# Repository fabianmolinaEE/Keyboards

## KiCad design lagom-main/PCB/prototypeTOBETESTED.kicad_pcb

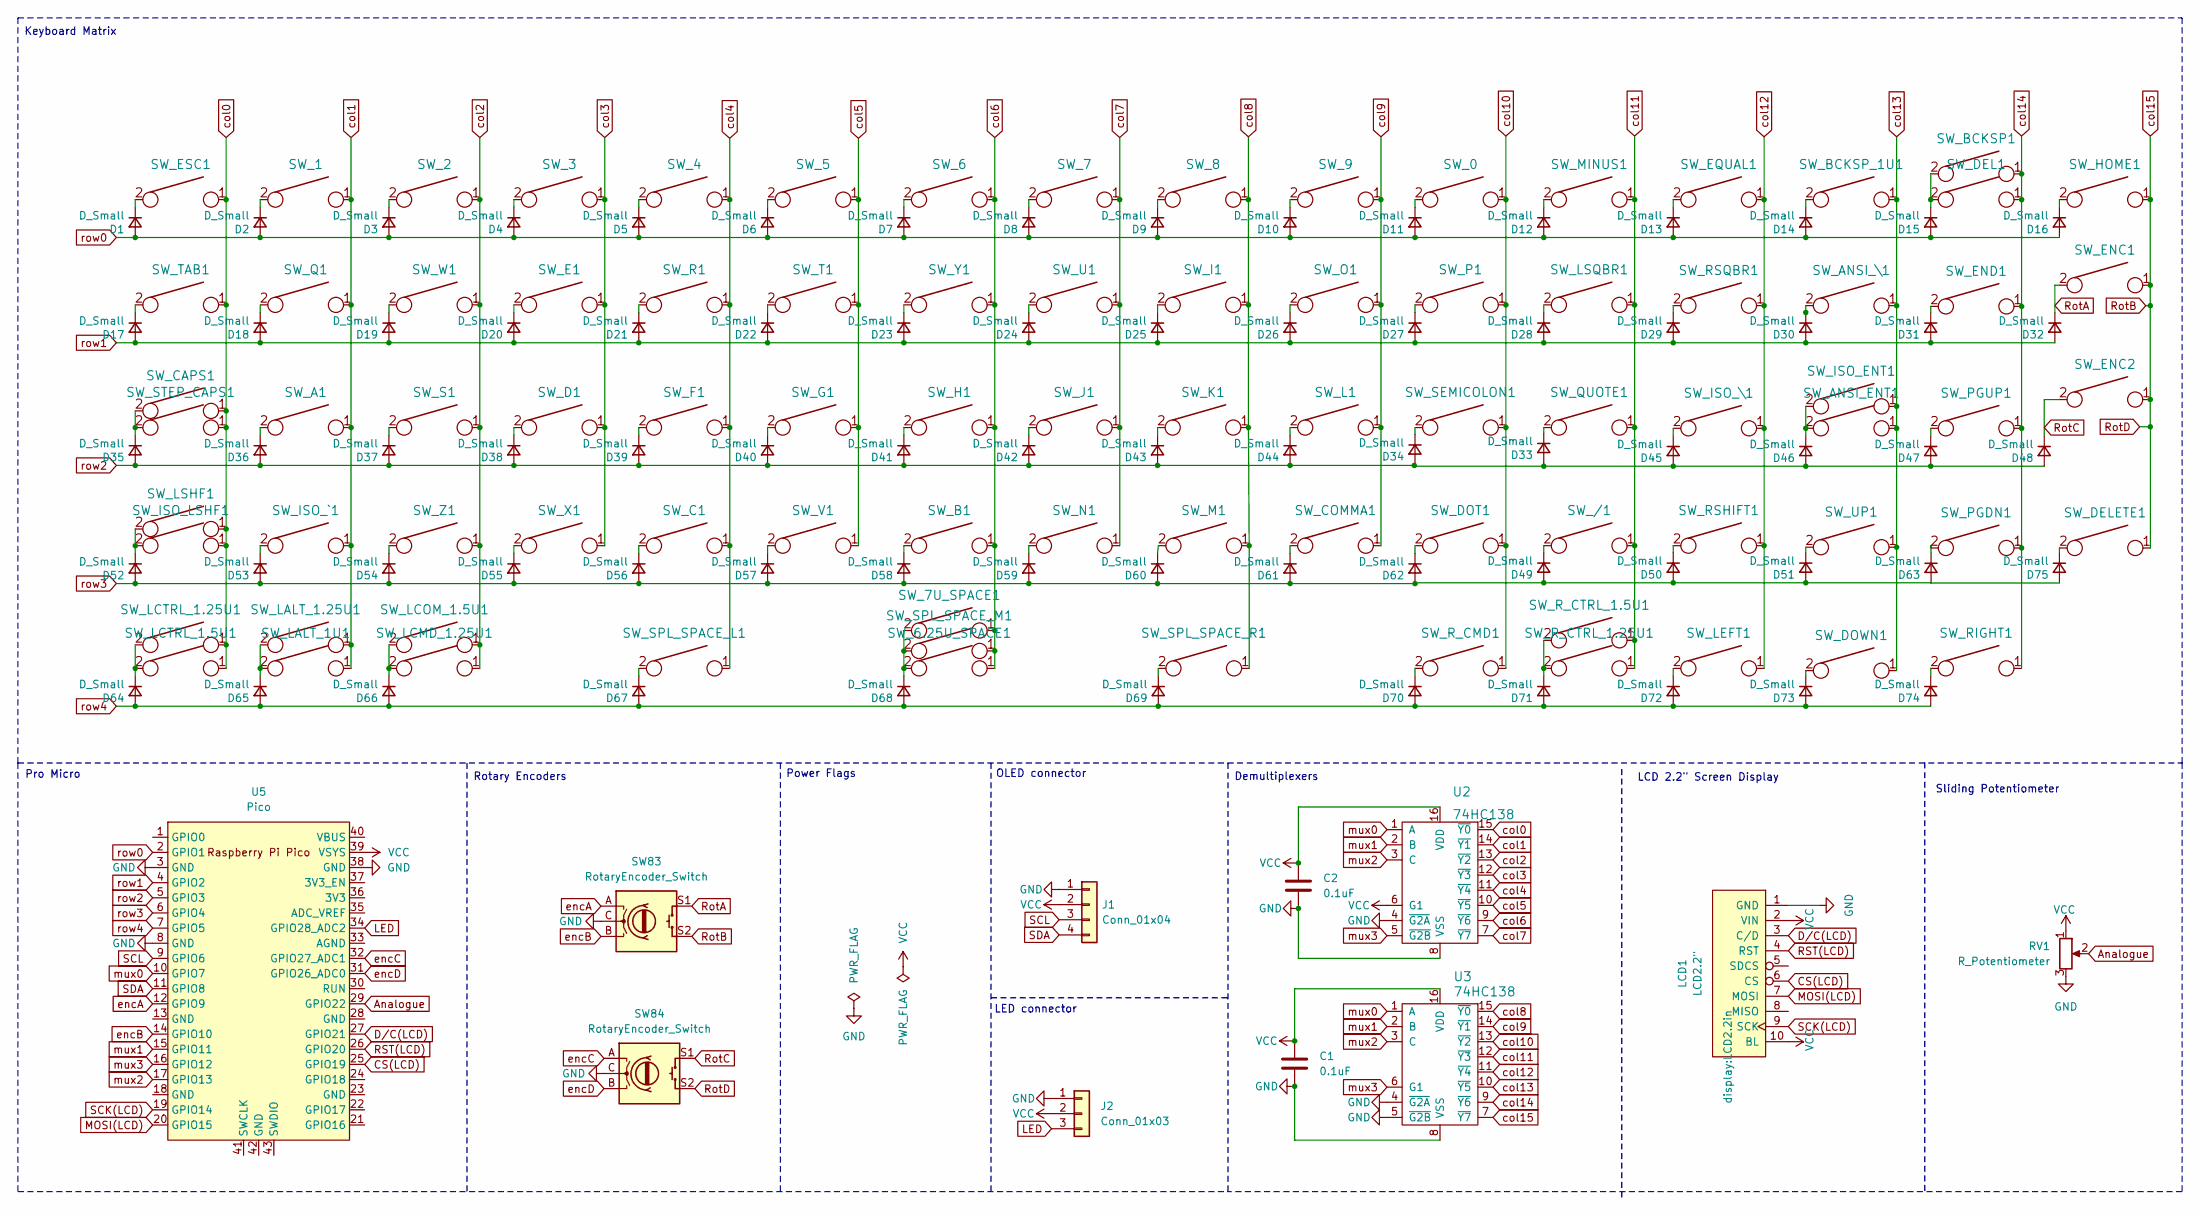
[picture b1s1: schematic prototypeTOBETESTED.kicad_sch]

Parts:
C1, C2: 0.1uF; C_Disc_D4.7mm_W2.5mm_P5.00mm
D1, D2, D3, D4, D5, D6, D7, D8, D9, D10, D11, D12, D13, D14, D15, D16, D17, D18, D19, D20, D21, D22, D23, D24, D25, D26, D27, D28, D29, D30, D31, D32, D33, D34, D35, D36, D37, D38, D39, D40, D41, D42, D43, D44, D45, D46, D47, D48, D49, D50, D51, D52, D53, D54, D55, D56, D57, D58, D59, D60, D61, D62, D63, D64, D65, D66, D67, D68, D69, D70, D71, D72, D73, D74, D75: D_Small; D_DO-34_SOD68_P7.62mm_Horizontal
J1: Conn_01x04; PinSocket_1x04_P2.54mm_Vertical
J2: Conn_01x03; PinSocket_1x03_P2.54mm_Vertical
LCD1: LCD2.2"; LCD2.2in
RV1: R_Potentiometer; Potentiometer_Bourns_PTA6043_Single_Slide
SW83, SW84: RotaryEncoder_Switch; RotaryEncoder_EC11
SW_0, SW_1, SW_2, SW_3, SW_4, SW_5, SW_6, SW_7, SW_8, SW_9: KEYSW; SW_Cherry_MX_1.00u_PCB
SW_6.25U_SPACE1: KEYSW; SW_Cherry_MX_6.25u_PCB
SW_7U_SPACE1: KEYSW; SW_Cherry_MX_7u_PCB
SW_/1: KEYSW; SW_Cherry_MX_1.00u_PCB
SW_A1: KEYSW; SW_Cherry_MX_1.00u_PCB
SW_ANSI_ENT1: KEYSW; SW_Cherry_MX_2.25u_PCB
SW_ANSI_\1: KEYSW; SW_Cherry_MX_1.50u_PCB
SW_B1: KEYSW; SW_Cherry_MX_1.00u_PCB
SW_BCKSP1: KEYSW; SW_Cherry_MX_2.00u_PCB
SW_BCKSP_1U1: KEYSW; SW_Cherry_MX_1.00u_PCB
SW_C1: KEYSW; SW_Cherry_MX_1.00u_PCB
SW_CAPS1: KEYSW; SW_Cherry_MX_1.75u_PCB
SW_COMMA1: KEYSW; SW_Cherry_MX_1.00u_PCB
SW_D1: KEYSW; SW_Cherry_MX_1.00u_PCB
SW_DEL1: KEYSW; SW_Cherry_MX_1.00u_PCB
SW_DELETE1: KEYSW; SW_Cherry_MX_1.00u_PCB
SW_DOT1: KEYSW; SW_Cherry_MX_1.00u_PCB
SW_DOWN1: KEYSW; SW_Cherry_MX_1.00u_PCB
SW_E1: KEYSW; SW_Cherry_MX_1.00u_PCB
SW_ENC1, SW_ENC2: KEYSW; SW_Cherry_MX_1.00u_PCB
SW_END1: KEYSW; SW_Cherry_MX_1.00u_PCB
SW_EQUAL1: KEYSW; SW_Cherry_MX_1.00u_PCB
SW_ESC1: KEYSW; SW_Cherry_MX_1.00u_PCB
SW_F1: KEYSW; SW_Cherry_MX_1.00u_PCB
SW_G1: KEYSW; SW_Cherry_MX_1.00u_PCB
SW_H1: KEYSW; SW_Cherry_MX_1.00u_PCB
SW_HOME1: KEYSW; SW_Cherry_MX_1.00u_PCB
SW_I1: KEYSW; SW_Cherry_MX_1.00u_PCB
SW_ISO_ENT1: KEYSW; SW_Cherry_MX_ISOEnter_PCB_Flipped_Rotated
SW_ISO_LSHF1: KEYSW; SW_Cherry_MX_1.25u_PCB
SW_ISO_\1: KEYSW; SW_Cherry_MX_1.00u_PCB
SW_ISO_`1: KEYSW; SW_Cherry_MX_1.00u_PCB
SW_J1: KEYSW; SW_Cherry_MX_1.00u_PCB
SW_K1: KEYSW; SW_Cherry_MX_1.00u_PCB
SW_L1: KEYSW; SW_Cherry_MX_1.00u_PCB
SW_LALT_1.25U1: KEYSW; SW_Cherry_MX_1.25u_PCB
SW_LALT_1U1: KEYSW; SW_Cherry_MX_1.00u_PCB
SW_LCMD_1.25U1: KEYSW; SW_Cherry_MX_1.25u_PCB
SW_LCOM_1.5U1: KEYSW; SW_Cherry_MX_1.50u_PCB
SW_LCTRL_1.5U1: KEYSW; SW_Cherry_MX_1.50u_PCB
SW_LCTRL_1.25U1: KEYSW; SW_Cherry_MX_1.25u_PCB
SW_LEFT1: KEYSW; SW_Cherry_MX_1.00u_PCB
SW_LSHF1: KEYSW; SW_Cherry_MX_2.25u_PCB
SW_LSQBR1: KEYSW; SW_Cherry_MX_1.00u_PCB
SW_M1: KEYSW; SW_Cherry_MX_1.00u_PCB
SW_MINUS1: KEYSW; SW_Cherry_MX_1.00u_PCB
SW_N1: KEYSW; SW_Cherry_MX_1.00u_PCB
SW_O1: KEYSW; SW_Cherry_MX_1.00u_PCB
SW_P1: KEYSW; SW_Cherry_MX_1.00u_PCB
SW_PGDN1: KEYSW; SW_Cherry_MX_1.00u_PCB
SW_PGUP1: KEYSW; SW_Cherry_MX_1.00u_PCB
SW_Q1: KEYSW; SW_Cherry_MX_1.00u_PCB
SW_QUOTE1: KEYSW; SW_Cherry_MX_1.00u_PCB
SW_R1: KEYSW; SW_Cherry_MX_1.00u_PCB
SW_RIGHT1: KEYSW; SW_Cherry_MX_1.00u_PCB
SW_RSHIFT1: KEYSW; SW_Cherry_MX_1.75u_PCB
SW_RSQBR1: KEYSW; SW_Cherry_MX_1.00u_PCB
SW_R_CMD1: KEYSW; SW_Cherry_MX_1.25u_PCB
SW_R_CTRL_1.5U1: KEYSW; SW_Cherry_MX_1.50u_PCB
SW_R_CTRL_1.25U1: KEYSW; SW_Cherry_MX_1.25u_PCB
SW_S1: KEYSW; SW_Cherry_MX_1.00u_PCB
SW_SEMICOLON1: KEYSW; SW_Cherry_MX_1.00u_PCB
SW_SPL_SPACE_L1: KEYSW; SW_Cherry_MX_2.25u_PCB
SW_SPL_SPACE_M1: KEYSW; SW_Cherry_MX_1.25u_PCB
SW_SPL_SPACE_R1: KEYSW; SW_Cherry_MX_2.75u_PCB
SW_STEP_CAPS1: KEYSW; SW_Cherry_MX_1.25u_PCB
SW_T1: KEYSW; SW_Cherry_MX_1.00u_PCB
SW_TAB1: KEYSW; SW_Cherry_MX_1.50u_Plate
SW_U1: KEYSW; SW_Cherry_MX_1.00u_PCB
SW_UP1: KEYSW; SW_Cherry_MX_1.00u_PCB
SW_V1: KEYSW; SW_Cherry_MX_1.00u_PCB
SW_W1: KEYSW; SW_Cherry_MX_1.00u_PCB
SW_X1: KEYSW; SW_Cherry_MX_1.00u_PCB
SW_Y1: KEYSW; SW_Cherry_MX_1.00u_PCB
SW_Z1: KEYSW; SW_Cherry_MX_1.00u_PCB
U2, U3: 74HC138; DIP-16_W7.62mm_Socket
U5: Pico; RPi_Pico_SMD_TH

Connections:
Analogue: RV1.2, U5.29 (GPIO22)
CS(LCD): LCD1.6 (CS), U5.25 (GPIO19)
D/C(LCD): LCD1.3 (C/D), U5.27 (GPIO21)
GND: C1.2, C2.2, J1.1, J2.1, LCD1.1 (GND), RV1.3, SW83.C, SW84.C, U2.4 (~G2A), U2.8 (VSS), U3.4 (~G2A), U3.5 (~G2B), U3.8 (VSS), U5.3 (GND), U5.8 (GND), U5.38 (GND)
LED: J2.3, U5.34 (GPIO28_ADC2)
MOSI(LCD): LCD1.7 (MOSI), U5.20 (GPIO15)
unnamed: D1.1 (K), SW_ESC1.2
unnamed: D2.1 (K), SW_1.2
unnamed: D3.1 (K), SW_2.2
unnamed: D4.1 (K), SW_3.2
unnamed: D5.1 (K), SW_4.2
unnamed: D6.1 (K), SW_5.2
unnamed: D7.1 (K), SW_6.2
unnamed: D8.1 (K), SW_7.2
unnamed: D9.1 (K), SW_8.2
unnamed: D10.1 (K), SW_9.2
unnamed: D11.1 (K), SW_0.2
unnamed: D12.1 (K), SW_MINUS1.2
unnamed: D13.1 (K), SW_EQUAL1.2
unnamed: D14.1 (K), SW_BCKSP_1U1.2
unnamed: D15.1 (K), SW_BCKSP1.2, SW_DEL1.2
unnamed: D16.1 (K), SW_HOME1.2
unnamed: D17.1 (K), SW_TAB1.2
unnamed: D18.1 (K), SW_Q1.2
unnamed: D19.1 (K), SW_W1.2
unnamed: D20.1 (K), SW_E1.2
unnamed: D21.1 (K), SW_R1.2
unnamed: D22.1 (K), SW_T1.2
unnamed: D23.1 (K), SW_Y1.2
unnamed: D24.1 (K), SW_U1.2
unnamed: D25.1 (K), SW_I1.2
unnamed: D26.1 (K), SW_O1.2
unnamed: D27.1 (K), SW_P1.2
unnamed: D28.1 (K), SW_LSQBR1.2
unnamed: D29.1 (K), SW_RSQBR1.2
unnamed: D30.1 (K), SW_ANSI_\1.2
unnamed: D31.1 (K), SW_END1.2
unnamed: D33.1 (K), SW_QUOTE1.2
unnamed: D34.1 (K), SW_SEMICOLON1.2
unnamed: D35.1 (K), SW_CAPS1.2, SW_STEP_CAPS1.2
unnamed: D36.1 (K), SW_A1.2
unnamed: D37.1 (K), SW_S1.2
unnamed: D38.1 (K), SW_D1.2
unnamed: D39.1 (K), SW_F1.2
unnamed: D40.1 (K), SW_G1.2
unnamed: D41.1 (K), SW_H1.2
unnamed: D42.1 (K), SW_J1.2
unnamed: D43.1 (K), SW_K1.2
unnamed: D44.1 (K), SW_L1.2
unnamed: D45.1 (K), SW_ISO_\1.2
unnamed: D46.1 (K), SW_ANSI_ENT1.2, SW_ISO_ENT1.2
unnamed: D47.1 (K), SW_PGUP1.2
unnamed: D49.1 (K), SW_/1.2
unnamed: D50.1 (K), SW_RSHIFT1.2
unnamed: D51.1 (K), SW_UP1.2
unnamed: D52.1 (K), SW_ISO_LSHF1.2, SW_LSHF1.2
unnamed: D53.1 (K), SW_ISO_`1.2
unnamed: D54.1 (K), SW_Z1.2
unnamed: D55.1 (K), SW_X1.2
unnamed: D56.1 (K), SW_C1.2
unnamed: D57.1 (K), SW_V1.2
unnamed: D58.1 (K), SW_B1.2
unnamed: D59.1 (K), SW_N1.2
unnamed: D60.1 (K), SW_M1.2
unnamed: D61.1 (K), SW_COMMA1.2
unnamed: D62.1 (K), SW_DOT1.2
unnamed: D63.1 (K), SW_PGDN1.2
unnamed: D64.1 (K), SW_LCTRL_1.5U1.2, SW_LCTRL_1.25U1.2
unnamed: D65.1 (K), SW_LALT_1.25U1.2, SW_LALT_1U1.2
unnamed: D66.1 (K), SW_LCMD_1.25U1.2, SW_LCOM_1.5U1.2
unnamed: D67.1 (K), SW_SPL_SPACE_L1.2
unnamed: D68.1 (K), SW_6.25U_SPACE1.2, SW_7U_SPACE1.2, SW_SPL_SPACE_M1.2
unnamed: D69.1 (K), SW_SPL_SPACE_R1.2
unnamed: D70.1 (K), SW_R_CMD1.2
unnamed: D71.1 (K), SW_R_CTRL_1.5U1.2, SW_R_CTRL_1.25U1.2
unnamed: D72.1 (K), SW_LEFT1.2
unnamed: D73.1 (K), SW_DOWN1.2
unnamed: D74.1 (K), SW_RIGHT1.2
unnamed: D75.1 (K), SW_DELETE1.2
RST(LCD): LCD1.4 (RST), U5.26 (GPIO20)
RotA: D32.1 (K), SW83.S1, SW_ENC1.2
RotB: SW83.S2, SW84.S2, SW_DELETE1.1, SW_ENC1.1, SW_ENC2.1, SW_HOME1.1, U3.7 (~Y7)
RotC: D48.1 (K), SW84.S1, SW_ENC2.2
SCK(LCD): LCD1.9 (SCK), U5.19 (GPIO14)
SCL: J1.3, U5.9 (GPIO6)
SDA: J1.4, U5.11 (GPIO8)
VCC: C1.1, C2.1, J1.2, J2.2, LCD1.2 (VIN), LCD1.10 (BL), RV1.1, U2.6 (G1), U2.16 (VDD), U3.16 (VDD), U5.39 (VSYS)
col0: SW_CAPS1.1, SW_ESC1.1, SW_ISO_LSHF1.1, SW_LCTRL_1.5U1.1, SW_LCTRL_1.25U1.1, SW_LSHF1.1, SW_STEP_CAPS1.1, SW_TAB1.1, U2.15 (~Y0)
col1: SW_1.1, SW_A1.1, SW_ISO_`1.1, SW_LALT_1.25U1.1, SW_LALT_1U1.1, SW_Q1.1, U2.14 (~Y1)
col2: SW_2.1, SW_LCMD_1.25U1.1, SW_LCOM_1.5U1.1, SW_S1.1, SW_W1.1, SW_Z1.1, U2.13 (~Y2)
col3: SW_3.1, SW_D1.1, SW_E1.1, SW_X1.1, U2.12 (~Y3)
col4: SW_4.1, SW_C1.1, SW_F1.1, SW_R1.1, SW_SPL_SPACE_L1.1, U2.11 (~Y4)
col5: SW_5.1, SW_G1.1, SW_T1.1, SW_V1.1, U2.10 (~Y5)
col6: SW_6.1, SW_6.25U_SPACE1.1, SW_7U_SPACE1.1, SW_B1.1, SW_H1.1, SW_SPL_SPACE_M1.1, SW_Y1.1, U2.9 (~Y6)
col7: SW_7.1, SW_J1.1, SW_N1.1, SW_U1.1, U2.7 (~Y7)
col8: SW_8.1, SW_I1.1, SW_K1.1, SW_M1.1, SW_SPL_SPACE_R1.1, U3.15 (~Y0)
col9: SW_9.1, SW_COMMA1.1, SW_L1.1, SW_O1.1, U3.14 (~Y1)
col10: SW_0.1, SW_DOT1.1, SW_P1.1, SW_R_CMD1.1, SW_SEMICOLON1.1, U3.13 (~Y2)
col11: SW_/1.1, SW_LSQBR1.1, SW_MINUS1.1, SW_QUOTE1.1, SW_R_CTRL_1.5U1.1, SW_R_CTRL_1.25U1.1, U3.12 (~Y3)
col12: SW_EQUAL1.1, SW_ISO_\1.1, SW_LEFT1.1, SW_RSHIFT1.1, SW_RSQBR1.1, U3.11 (~Y4)
col13: SW_ANSI_ENT1.1, SW_ANSI_\1.1, SW_BCKSP_1U1.1, SW_DOWN1.1, SW_ISO_ENT1.1, SW_UP1.1, U3.10 (~Y5)
col14: SW_BCKSP1.1, SW_DEL1.1, SW_END1.1, SW_PGDN1.1, SW_PGUP1.1, SW_RIGHT1.1, U3.9 (~Y6)
encA: SW83.A, U5.12 (GPIO9)
encB: SW83.B, U5.14 (GPIO10)
encC: SW84.A, U5.32 (GPIO27_ADC1)
encD: SW84.B, U5.31 (GPIO26_ADC0)
mux0: U2.1 (A), U3.1 (A), U5.10 (GPIO7)
mux1: U2.2 (B), U3.2 (B), U5.15 (GPIO11)
mux2: U2.3 (C), U3.3 (C), U5.17 (GPIO13)
mux3: U2.5 (~G2B), U3.6 (G1), U5.16 (GPIO12)
row0: D1.2 (A), D2.2 (A), D3.2 (A), D4.2 (A), D5.2 (A), D6.2 (A), D7.2 (A), D8.2 (A), D9.2 (A), D10.2 (A), D11.2 (A), D12.2 (A), D13.2 (A), D14.2 (A), D15.2 (A), D16.2 (A), U5.2 (GPIO1)
row1: D17.2 (A), D18.2 (A), D19.2 (A), D20.2 (A), D21.2 (A), D22.2 (A), D23.2 (A), D24.2 (A), D25.2 (A), D26.2 (A), D27.2 (A), D28.2 (A), D29.2 (A), D30.2 (A), D31.2 (A), D32.2 (A), U5.4 (GPIO2)
row2: D33.2 (A), D34.2 (A), D35.2 (A), D36.2 (A), D37.2 (A), D38.2 (A), D39.2 (A), D40.2 (A), D41.2 (A), D42.2 (A), D43.2 (A), D44.2 (A), D45.2 (A), D46.2 (A), D47.2 (A), D48.2 (A), U5.5 (GPIO3)
row3: D49.2 (A), D50.2 (A), D51.2 (A), D52.2 (A), D53.2 (A), D54.2 (A), D55.2 (A), D56.2 (A), D57.2 (A), D58.2 (A), D59.2 (A), D60.2 (A), D61.2 (A), D62.2 (A), U5.6 (GPIO4)
row4: D64.2 (A), D65.2 (A), D66.2 (A), D67.2 (A), D68.2 (A), D69.2 (A), D70.2 (A), D71.2 (A), D72.2 (A), D73.2 (A), D74.2 (A), U5.7 (GPIO5)

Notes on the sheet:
OLED connector
Rotary Encoders
LCD 2.2" Screen Display
Keyboard Matrix
Power Flags
LED connector
Pro Micro
Sliding Potentiometer
Demultiplexers

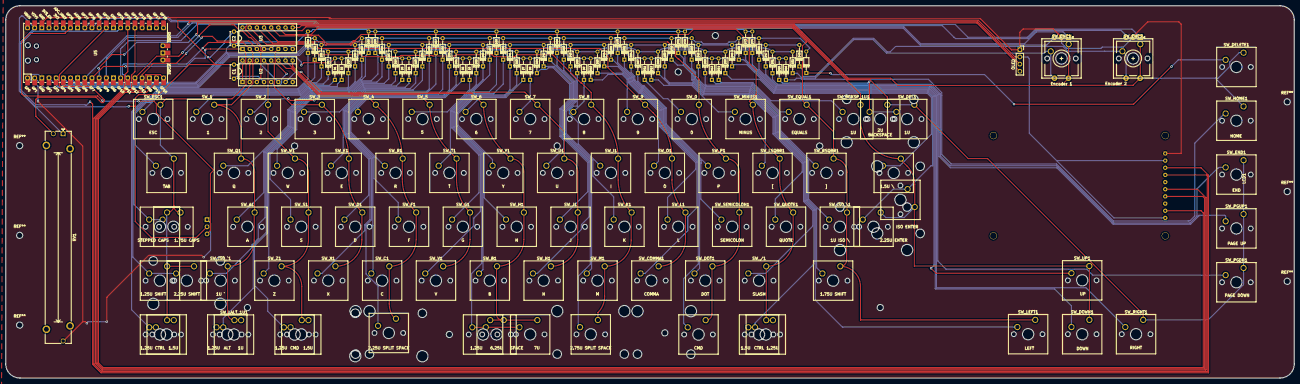
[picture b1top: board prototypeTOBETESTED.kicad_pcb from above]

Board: 2 copper layers, 456.9 x 132.0 mm, 171 parts (1 on the bottom side), 115 nets.

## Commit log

2024-08-28 Uploaded Lagom's Keyboard to Modify
2024-08-30 Changed PCB To Use a RPI Pico and Fixed Wiring Routes
2024-09-09 finalizing
2024-09-09 mylib
2024-09-11 Finalized PCB and Cover. Added Gerbers
